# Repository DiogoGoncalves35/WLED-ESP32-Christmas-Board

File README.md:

# WLED ESP32 Christmas Board

This board is designed to control 4 x WS2812B string lights (Max 3A Total) via WLED software, and it was added a 4A fuse to protect. Max current for the 4 strings is about 3A, and 1A is left to ESP32.   

Board was tested with 2 x WS2812B 5 meter string lights, each draws arround 400-600 mA with color white and brightness at 100%. WLED version was [v0.14.0 "Hoshi"](https://github.com/Aircoookie/WLED/releases/tag/v0.14.0).

------------

### Schematic 

The [schematic](/PCB/Schematic.pdf) is arround ESP32 WROOM 32E microcontroller. A 4A fuse was added to protect the circuit in case of short circuit, the AMS1117 regulates the input voltage to 3.3V and powers the ESP32.

------------

### PCB

[This](/PCB) 1.6mm board contains 4 layers with the stackup Signal+Power/GND/GND/Signal+Power.The connector on the right is for programming and it works with pogo pins.  

------------

### Known issues

- Some noise on TX/RX lines, sometimes [this](https://user-images.githubusercontent.com/64553282/108736433-e6be2380-7531-11eb-8186-5ca70f359cc5.PNG) appears and causes board to crash, by connecting pogo pins withot any connection to a programmer board fixed the issue

------------

### To-Do

- Fixing noise on TX/RX lines

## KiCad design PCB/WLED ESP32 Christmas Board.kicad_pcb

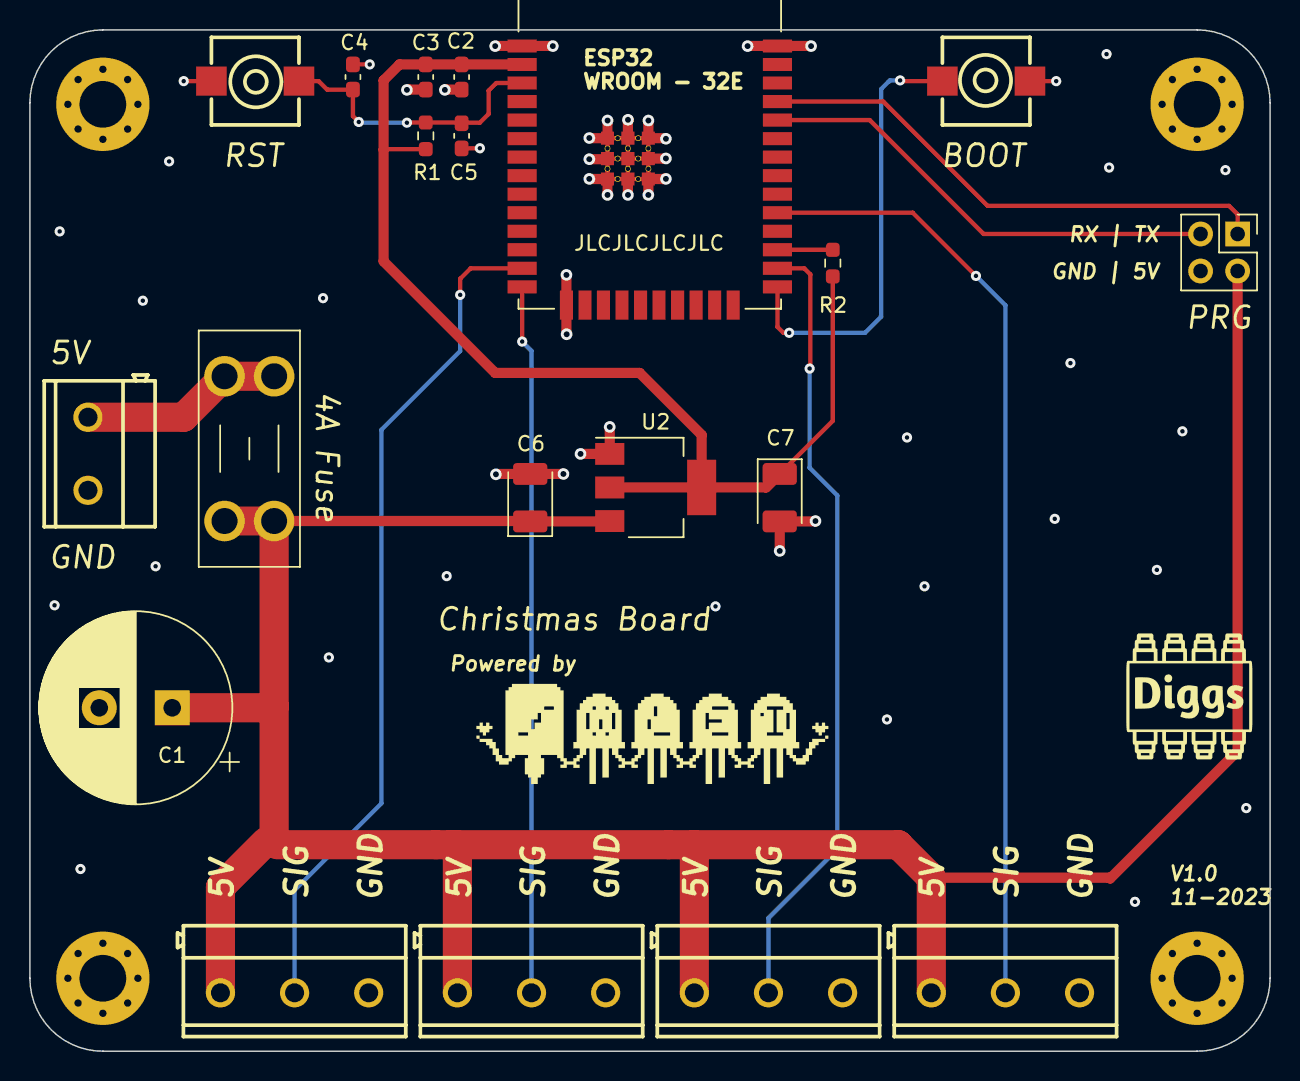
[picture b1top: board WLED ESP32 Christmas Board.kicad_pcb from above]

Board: 4 copper layers, 85.0 x 70.0 mm, 20 parts (0 on the bottom side), 13 nets.

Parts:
C1: 100 uF; CP_Radial_D13.0mm_P5.00mm
C2, C4: 0.1 uF; C_0603_1608Metric_Pad1.08x0.95mm_HandSolder
C3: 10 uF; C_0603_1608Metric_Pad1.08x0.95mm_HandSolder
C5: 1 uF; C_0603_1608Metric_Pad1.08x0.95mm_HandSolder
C6, C7: 100 uF; CP_EIA-3528-21_Kemet-B_Pad1.50x2.35mm_HandSolder
F1: 4A; Fuseholder_Blade_Mini_Keystone_3568
J1: IN; 2P
J2: Pogo Pins; PinHeader_2x02_P2.54mm_Vertical
J3: OUT 1; 3P
J4: OUT 2; 3P
J5: OUT 3; 3P
J6: OUT 4; 3P
R1, R2: 10k; R_0603_1608Metric_Pad0.98x0.95mm_HandSolder
SW1: RST; SMD Switch
SW2: BOOT; SMD Switch
U1: ESP32WROOM-32E__16MB_; XCVR_ESP32-WROOM-32E__16MB_
U2: AMS1117-3.3; SOT-223-3_TabPin2

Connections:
+3.3V: C2.2, C3.1, C7.1, R1.1, R2.2, U1.2 (3V3), U2.2 (VO)
+5V: C1.1, C6.1, F1.2, J2.2, J3.1, J4.1, J5.1, J6.1, U2.3 (VI)
/BOOT: SW2.1, U1.25 (IO0)
/DOUT_1: J3.2, U1.13 (IO14)
/DOUT_2: J4.2, U1.14 (IO12)
/DOUT_3: J5.2, U1.26 (IO4)
/DOUT_4: J6.2, U1.29 (IO5)
/ESP32_EN: C4.1, C5.2, R1.2, SW1.1, U1.3 (EN)
/ESP32_RX: J2.3, U1.34 (RXD0)
/ESP32_TX: J2.1, U1.35 (TXD0)
GND: C1.2, C2.1, C3.2, C4.2, C5.1, C6.2, C7.2, J1.2, J2.4, J3.3, J4.3, J5.3, J6.3, SW1.2, SW2.2, U1.1 (GND), U1.15 (GND), U1.38 (GND), U1.39_1 (GND), U1.39_2 (GND), U1.39_3 (GND), U1.39_4 (GND), U1.39_5 (GND), U1.39_6 (GND), U1.39_7 (GND), U1.39_8 (GND), U1.39_9 (GND), U1.39_10, U1.39_11, U1.39_12, U1.39_13, U1.39_14, U1.39_15, U1.39_16, U1.39_17, U1.39_18, U1.39_19, U1.39_20, U1.39_21, U2.1 (GND)
unnamed: F1.1, J1.1
unnamed: R2.1, U1.27 (IO16)
